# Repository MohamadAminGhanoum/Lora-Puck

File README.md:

# Lora-Puck
im planning on doing the lorapuck, while adding some simple and accurate sensors, which certainly will make this Lora Puck a lot more useful to me. Im planning to make 2 pcbs, one i keep at home that can track the temperature of e.g my room, and one i can take with me anywhere, and this will allow me to recieve signals from my home LORA, and i will be recieving it to my other LORA puc that i carry with me.
NOTE: as i am making it in the EU, i should follow the european law of max. 868 MHz, and not 915 MHz like USA

## Schematics:

## PCB:

## 3d pic of pcb:

## BOM

|Name             |Vendor                 |Quantity|Price in USD|Link                                                                                                                                                                                                    |
|-----------------|-----------------------|--------|------------|--------------------------------------------------------------------------------------------------------------------------------------------------------------------------------------------------------|
|PCB              |JLCPCB                 |5       |10          |JLCPCB                                                                                                                                                                                                  |
|100nF capacitor  |LCSC                   |12      |self-sourced|                                                                                                                                                                                                        |
|47nH inductor    |LCSC                   |1       |0.23        |https://www.lcsc.com/product-detail/C440659.html?spm=wm.gwc.xh.4.tp___wm.ddx.ssl.gwc&lcsc_vid=QAMKAlFUFVZXUFcCTgNWBgcHQQVYBlQEFlBWAlJSEgIxVlNeQ1RXU1ZUTlhZVzsOAxUeFF5JWBEPFBcWGBMaSQgFBAJABAsLWA%3D%3D  |
|HTU21D           |LCSC                   |2       |3.29        |https://www.lcsc.com/product-detail/C83479.html?spm=wm.gwc.xh.1.tp___wm.ddx.ssl.gwc&lcsc_vid=QAMKAlFUFVZXUFcCTgNWBgcHQQVYBlQEFlBWAlJSEgIxVlNeQ1RXU1ZUTlhZVzsOAxUeFF5JWBEPFBcWGBMaSQgFBAJABAsLWA%3D%3D   |
|RP2040           |LCSC                   |2       |1.99        |https://www.lcsc.com/product-detail/C2040.html?spm=wm.gwc.xh.2.tp___wm.ddx.ssl.gwc&lcsc_vid=QAMKAlFUFVZXUFcCTgNWBgcHQQVYBlQEFlBWAlJSEgIxVlNeQ1RXU1ZUTlhZVzsOAxUeFF5JWBEPFBcWGBMaSQgFBAJABAsLWA%3D%3D    |
|SX1262IMLTRT     |LCSC                   |2       |6.51        |https://www.lcsc.com/product-detail/C191341.html?spm=wm.gwc.xh.3.tp___wm.ddx.ssl.gwc&lcsc_vid=QAMKAlFUFVZXUFcCTgNWBgcHQQVYBlQEFlBWAlJSEgIxVlNeQ1RXU1ZUTlhZVzsOAxUeFF5JWBEPFBcWGBMaSQgFBAJABAsLWA%3D%3D  |
|                 |                       |        |            |                                                                                                                                                                                                        |
|AP2112K-3.3TRG1  |LCSC                   |5       |0.55        |https://www.lcsc.com/product-detail/C23380830.html?spm=wm.gwc.xh.5.tp___wm.ddx.ssl.gwc&lcsc_vid=QAMKAlFUFVZXUFcCTgNWBgcHQQVYBlQEFlBWAlJSEgIxVlNeQ1RXU1ZUTlhZVzsOAxUeFF5JWBEPFBcWGBMaSQgFBAJABAsLWA%3D%3D|
|W25Q128JVS       |LCSC                   |2       |5.6         |https://www.lcsc.com/product-detail/C97521.html?spm=wm.gwc.xh.6.tp___wm.ddx.ssl.gwc&lcsc_vid=QAMKAlFUFVZXUFcCTgNWBgcHQQVYBlQEFlBWAlJSEgIxVlNeQ1RXU1ZUTlhZVzsOAxUeFF5JWBEPFBcWGBMaSQgFBAJABAsLWA%3D%3D   |
|10uF capacitor   |LCSC                   |50      |1.75        |https://www.lcsc.com/product-detail/C1691.html?spm=wm.gwc.xh.7.tp___wm.ddx.ssl.gwc&lcsc_vid=QAMKAlFUFVZXUFcCTgNWBgcHQQVYBlQEFlBWAlJSEgIxVlNeQ1RXU1ZUTlhZVzsOAxUeFF5JWBEPFBcWGBMaSQgFBAJABAsLWA%3D%3D    |
|12nHz crystal    |LCSC                   |20      |0.43        |https://www.lcsc.com/product-detail/C1332832.html?spm=wm.gwc.xh.8.tp___wm.ddx.ssl.gwc&lcsc_vid=QAMKAlFUFVZXUFcCTgNWBgcHQQVYBlQEFlBWAlJSEgIxVlNeQ1RXU1ZUTlhZVzsOAxUeFF5JWBEPFBcWGBMaSQgFBAJABAsLWA%3D%3D |
|470nF cap        |LCSC                   |100     |1.15        |https://www.lcsc.com/product-detail/C105526.html?spm=wm.gwc.xh.9.tp___wm.ddx.ssl.gwc&lcsc_vid=QAMKAlFUFVZXUFcCTgNWBgcHQQVYBlQEFlBWAlJSEgIxVlNeQ1RXU1ZUTlhZVzsOAxUeFF5JWBEPFBcWGBMaSQgFBAJABAsLWA%3D%3D  |
|1k resistor      |LCSC                   |100     |0.76        |https://www.lcsc.com/product-detail/C2907002.html?spm=wm.gwc.xh.10.tp___wm.ddx.ssl.gwc&lcsc_vid=QAMKAlFUFVZXUFcCTgNWBgcHQQVYBlQEFlBWAlJSEgIxVlNeQ1RXU1ZUTlhZVzsOAxUeFF5JWBEPFBcWGBMaSQgFBAJABAsLWA%3D%3D|
|0900FM15K0039001E|LCSC                   |1       |0.61        |https://www.lcsc.com/product-detail/C7434807.html?spm=wm.gwc.xh.0.tp___wm.ddx.ssl.gwc&lcsc_vid=QAMKAlFUFVZXUFcCTgNWBgcHQQVYBlQEFlBWAlJSEgIxVlNeQ1RXU1ZUTlhZVzsOAxUeFF5JWBEPFBcWGBMaSQgFBAJABAsLWA%3D%3D |
|100 ohm resistor |LCSC                   |1       |selfsourced |                                                                                                                                                                                                        |
|32MHz            |LCSC                   |2       |selfsourced |                                                                                                                                                                                                        |
|3.3pF capacitor  |LCSC                   |100     |1.04        |https://www.lcsc.com/product-detail/C1660.html?spm=wm.gwc.xh.11.tp___wm.ddx.ssl.gwc&lcsc_vid=QAMKAlFUFVZXUFcCTgNWBgcHQQVYBlQEFlBWAlJSEgIxVlNeQ1RXU1ZUTlhZVzsOAxUeFF5JWBEPFBcWGBMaSQgFBAJABAsLWA%3D%3D   |
| 1uF capacitor   |LCSC                   |50      |1.09        |https://www.lcsc.com/product-detail/C29936.html?spm=wm.gwc.xh.12.tp___wm.ddx.ssl.gwc&lcsc_vid=QAMKAlFUFVZXUFcCTgNWBgcHQQVYBlQEFlBWAlJSEgIxVlNeQ1RXU1ZUTlhZVzsOAxUeFF5JWBEPFBcWGBMaSQgFBAJABAsLWA%3D%3D  |
|5.1k resistor    |LCSC                   |100     |0.24        |https://www.lcsc.com/product-detail/C2907044.html?spm=wm.gwc.xh.13.tp___wm.ddx.ssl.gwc&lcsc_vid=QAMKAlFUFVZXUFcCTgNWBgcHQQVYBlQEFlBWAlJSEgIxVlNeQ1RXU1ZUTlhZVzsOAxUeFF5JWBEPFBcWGBMaSQgFBAJABAsLWA%3D%3D|
|USB-c            |LCSC                   |20      |1.41        |https://www.lcsc.com/product-detail/C2765186.html?spm=wm.gwc.xh.14.tp___wm.ddx.ssl.gwc&lcsc_vid=QAMKAlFUFVZXUFcCTgNWBgcHQQVYBlQEFlBWAlJSEgIxVlNeQ1RXU1ZUTlhZVzsOAxUeFF5JWBEPFBcWGBMaSQgFBAJABAsLWA%3D%3D|
|switch           |LCSC                   |2       |selfsourced |                                                                                                                                                                                                        |
|BLM15AX102SN1D   |LCSC                   |100     |1.26        |https://www.lcsc.com/product-detail/C85815.html?spm=wm.gwc.xh.15.tp___wm.ddx.ssl.gwc&lcsc_vid=QAMKAlFUFVZXUFcCTgNWBgcHQQVYBlQEFlBWAlJSEgIxVlNeQ1RXU1ZUTlhZVzsOAxUeFF5JWBEPFBcWGBMaSQgFBAJABAsLWA%3D%3D  |
|27.4 ohm resistor|LCSC                   |2       |selfsourced |                                                                                                                                                                                                        |
|1nF capacitor    |LCSC                   |1       |1.46        |https://www.lcsc.com/product-detail/C100040.html?spm=wm.gwc.xh.20.tp___wm.ddx.ssl.gwc&lcsc_vid=QAMKAlFUFVZXUFcCTgNWBgcHQQVYBlQEFlBWAlJSEgIxVlNeQ1RXU1ZUTlhZVzsOAxUeFF5JWBEPFBcWGBMaSQgFBAJABAsLWA%3D%3D |
| 39pF cap        |LCSC                   |100     |0.52        |https://www.lcsc.com/product-detail/C107049.html?spm=wm.gwc.xh.16.tp___wm.ddx.ssl.gwc&lcsc_vid=QAMKAlFUFVZXUFcCTgNWBgcHQQVYBlQEFlBWAlJSEgIxVlNeQ1RXU1ZUTlhZVzsOAxUeFF5JWBEPFBcWGBMaSQgFBAJABAsLWA%3D%3D |
| 15pF cap        |LCSC                   |100     |0.57        |https://www.lcsc.com/product-detail/C107037.html?spm=wm.gwc.xh.17.tp___wm.ddx.ssl.gwc&lcsc_vid=QAMKAlFUFVZXUFcCTgNWBgcHQQVYBlQEFlBWAlJSEgIxVlNeQ1RXU1ZUTlhZVzsOAxUeFF5JWBEPFBcWGBMaSQgFBAJABAsLWA%3D%3D |
| 47pF cap        |LCSC                   |100     |0.61        |https://www.lcsc.com/product-detail/C105622.html?spm=wm.gwc.xh.18.tp___wm.ddx.ssl.gwc&lcsc_vid=QAMKAlFUFVZXUFcCTgNWBgcHQQVYBlQEFlBWAlJSEgIxVlNeQ1RXU1ZUTlhZVzsOAxUeFF5JWBEPFBcWGBMaSQgFBAJABAsLWA%3D%3D |
| 9.1nH inductor  |LCSC                   |50      |0.54        |https://www.lcsc.com/product-detail/C395094.html?spm=wm.gwc.xh.19.tp___wm.ddx.ssl.gwc&lcsc_vid=QAMKAlFUFVZXUFcCTgNWBgcHQQVYBlQEFlBWAlJSEgIxVlNeQ1RXU1ZUTlhZVzsOAxUeFF5JWBEPFBcWGBMaSQgFBAJABAsLWA%3D%3D |
| 10k resistor    |LCSC                   |100     |0.51        |https://www.lcsc.com/product-detail/C98220.html?spm=wm.gwc.dh.21.tp___wm.ddx.ssl.gwc&lcsc_vid=QAMKAlFUFVZXUFcCTgNWBgcHQQVYBlQEFlBWAlJSEgIxVlNeQ1RXU1ZUTlhZVzsOAxUeFF5JWBEPFBcWGBMaSQgFBAJABAsLWA%3D%3D  |
|PE4259           |LCSC                   |2       |1.41        |https://www.lcsc.com/product-detail/C470892.html?spm=wm.gwc.xh.22.tp___wm.ddx.ssl.gwc&lcsc_vid=QAMKAlFUFVZXUFcCTgNWBgcHQQVYBlQEFlBWAlJSEgIxVlNeQ1RXU1ZUTlhZVzsOAxUeFF5JWBEPFBcWGBMaSQgFBAJABAsLWA%3D%3D |
|15uH inductor    |LCSC                   |20      |0.73        |https://www.lcsc.com/product-detail/C486329.html?spm=wm.gwc.xh.23.tp___wm.ddx.ssl.gwc&lcsc_vid=QAMKAlFUFVZXUFcCTgNWBgcHQQVYBlQEFlBWAlJSEgIxVlNeQ1RXU1ZUTlhZVzsOAxUeFF5JWBEPFBcWGBMaSQgFBAJABAsLWA%3D%3D |
|                 |                       |        |            |                                                                                                                                                                                                        |
|                 |Total cost w. shipping:|50 usd  |            |                                                                                                                                                                                                        |

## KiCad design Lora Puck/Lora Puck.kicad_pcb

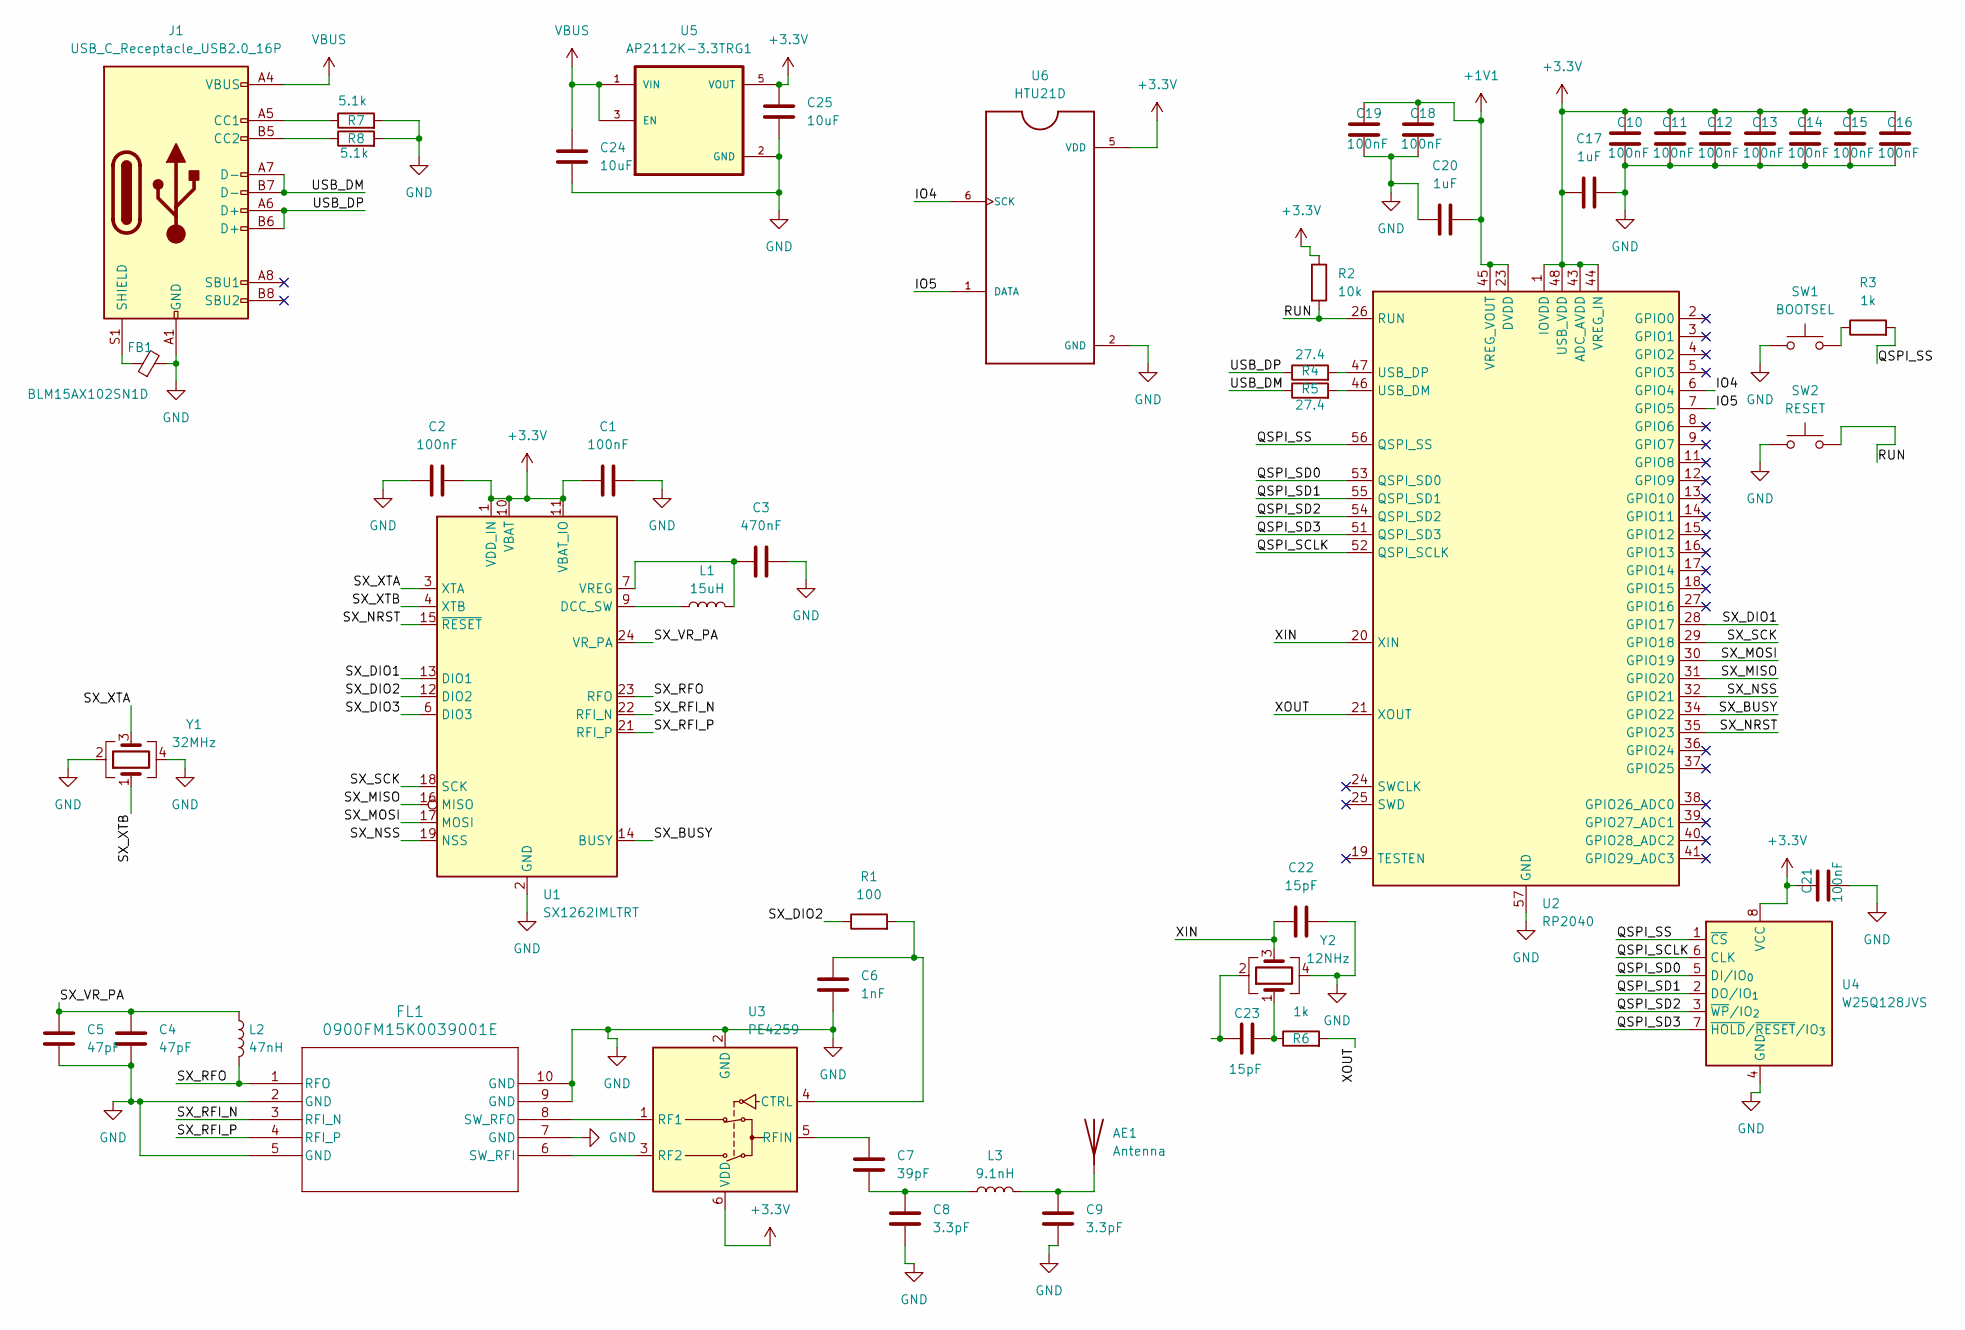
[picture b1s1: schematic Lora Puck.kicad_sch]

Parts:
AE1: Antenna; PinSocket_1x01_P2.54mm_Vertical
C1, C2, C10, C11, C12, C13, C14, C15, C16, C18, C19, C21: 100nF; C_0603_1608Metric
C3: 470nF; C_0603_1608Metric
C4, C5: 47pF; C_0603_1608Metric
C6: 1nF; C_0603_1608Metric
C7: 39pF; C_0603_1608Metric
C8, C9: 3.3pF; C_0603_1608Metric
C17, C20: 1uF; C_0603_1608Metric
C22, C23: 15pF; C_0603_1608Metric
C24, C25: 10uF; C_0603_1608Metric
FB1: BLM15AX102SN1D; L_0603_1608Metric
FL1: 0900FM15K0039001E; Balun_Johanson_0900FM15K0039
J1: USB_C_Receptacle_USB2.0_16P; USB_C_Receptacle_GCT_USB4105-xx-A_16P_TopMnt_Horizontal
L1: 15uH; L_0603_1608Metric
L2: 47nH; L_0603_1608Metric
L3: 9.1nH; L_0603_1608Metric
R1: 100; R_0603_1608Metric
R2: 10k; R_0603_1608Metric
R3, R6: 1k; R_0603_1608Metric
R4, R5: 27.4; R_0603_1608Metric
R7, R8: 5.1k; R_0603_1608Metric
SW1: BOOTSEL; SW_Tactile_SPST_NO_Straight_CK_PTS636Sx25SMTRLFS
SW2: RESET; SW_Tactile_SPST_NO_Straight_CK_PTS636Sx25SMTRLFS
U1: SX1262IMLTRT; QFN-24-1EP_4x4mm_P0.5mm_EP2.6x2.6mm
U2: RP2040; QFN-56-1EP_7x7mm_P0.4mm_EP3.2x3.2mm
U3: PE4259; SOT-363_SC-70-6
U4: W25Q128JVS; SOIC-8_5.3x5.3mm_P1.27mm
U5: AP2112K-3.3TRG1; SOT95P285X140-5N; PARTREV 2-2
U6: HTU21D; QFN100P300X300X100-7N
Y1: 32MHz; Crystal_SMD_3225-4Pin_3.2x2.5mm
Y2: 12NHz; Crystal_SMD_Abracon_ABM8G-4Pin_3.2x2.5mm

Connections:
+1V1: C18.1, C19.1, C20.2, U2.23 (DVDD), U2.45 (VREG_VOUT), U2.50 (DVDD)
+3.3V: C1.1, C2.2, C10.1, C11.1, C12.1, C13.1, C14.1, C15.1, C16.1, C17.1, C21.1, C25.1, R2.1, U1.1 (VDD_IN), U1.10 (VBAT), U1.11 (VBAT_IO), U2.1 (IOVDD), U2.10 (IOVDD), U2.22 (IOVDD), U2.33 (IOVDD), U2.42 (IOVDD), U2.43 (ADC_AVDD), U2.44 (VREG_IN), U2.48 (USB_VDD), U2.49 (IOVDD), U3.6 (VDD), U4.8 (VCC), U5.5 (VOUT), U6.5 (VDD)
/IO4: U2.6 (GPIO4), U6.6 (SCK)
/IO5: U2.7 (GPIO5), U6.1 (DATA)
/QSPI_SCLK: U2.52 (QSPI_SCLK), U4.6 (CLK)
/QSPI_SD0: U2.53 (QSPI_SD0), U4.5 (DI/IO_{0})
/QSPI_SD1: U2.55 (QSPI_SD1), U4.2 (DO/IO_{1})
/QSPI_SD2: U2.54 (QSPI_SD2), U4.3 (~WP/IO_{2})
/QSPI_SD3: U2.51 (QSPI_SD3), U4.7 (~HOLD/~RESET/IO_{3})
/QSPI_SS: R3.2, U2.56 (QSPI_SS), U4.1 (~CS)
/RUN: R2.2, SW2.2, U2.26 (RUN)
/SX_BUSY: U1.14 (BUSY), U2.34 (GPIO22)
/SX_DIO1: U1.13 (DIO1), U2.28 (GPIO17)
/SX_DIO2: R1.1, U1.12 (DIO2)
/SX_DIO3: U1.6 (DIO3)
/SX_MISO: U1.16 (MISO), U2.31 (GPIO20)
/SX_MOSI: U1.17 (MOSI), U2.30 (GPIO19)
/SX_NRST: U1.15 (~RESET), U2.35 (GPIO23)
/SX_NSS: U1.19 (NSS), U2.32 (GPIO21)
/SX_RFI_N: FL1.3 (RFI_N), U1.22 (RFI_N)
/SX_RFI_P: FL1.4 (RFI_P), U1.21 (RFI_P)
/SX_RFO: FL1.1 (RFO), L2.2, U1.23 (RFO)
/SX_SCK: U1.18 (SCK), U2.29 (GPIO18)
/SX_VR_PA: C4.1, C5.1, L2.1, U1.24 (VR_PA)
/SX_XTA: U1.3 (XTA), Y1.3
/SX_XTB: U1.4 (XTB), Y1.1
/USB_DM: J1.A7 (D-), J1.B7 (D-), R5.1
/USB_DP: J1.A6 (D+), J1.B6 (D+), R4.1
/XIN: C22.1, U2.20 (XIN), Y2.3
/XOUT: R6.2, U2.21 (XOUT)
GND: C1.2, C2.1, C3.2, C4.2, C5.2, C6.2, C8.1, C9.2, C10.2, C11.2, C12.2, C13.2, C14.2, C15.2, C16.2, C17.2, C18.2, C19.2, C20.1, C21.2, C22.2, C24.2, C25.2, FB1.2, FL1.2 (GND), FL1.5 (GND), FL1.7 (GND), FL1.9 (GND), FL1.10 (GND), J1.A1 (GND), J1.A12 (GND), J1.B1 (GND), J1.B12 (GND), R7.2, R8.2, SW1.1, SW2.1, U1.2 (GND), U1.5 (GND), U1.8 (GND), U1.20 (GND), U1.25 (GND), U2.57 (GND), U3.2 (GND), U4.4 (GND), U5.2 (GND), U6.2 (GND), U6.PAD (GND), Y1.2, Y1.4, Y2.4
unnamed: AE1.1 (A), C9.1, L3.2
unnamed: C7.1, C8.2, L3.1
unnamed: C23.1, Y2.2
unnamed: C23.2, R6.1, Y2.1
unnamed: FL1.6 (SW_RFI), U3.3 (RF2)
unnamed: FL1.8 (SW_RFO), U3.1 (RF1)
unnamed: J1.A5 (CC1), R7.1
unnamed: J1.B5 (CC2), R8.1
unnamed: FB1.1, J1.S1 (SHIELD)
unnamed: R3.1, SW1.2
unnamed: L1.1, U1.9 (DCC_SW)
unnamed: C3.1, L1.2, U1.7 (VREG)
unnamed: R5.2, U2.46 (USB_DM)
unnamed: R4.2, U2.47 (USB_DP)
unnamed: C6.1, R1.2, U3.4 (CTRL)
unnamed: C7.2, U3.5 (RFIN)
VBUS: C24.1, J1.A4 (VBUS), J1.A9 (VBUS), J1.B4 (VBUS), J1.B9 (VBUS), U5.1 (VIN), U5.3 (EN)

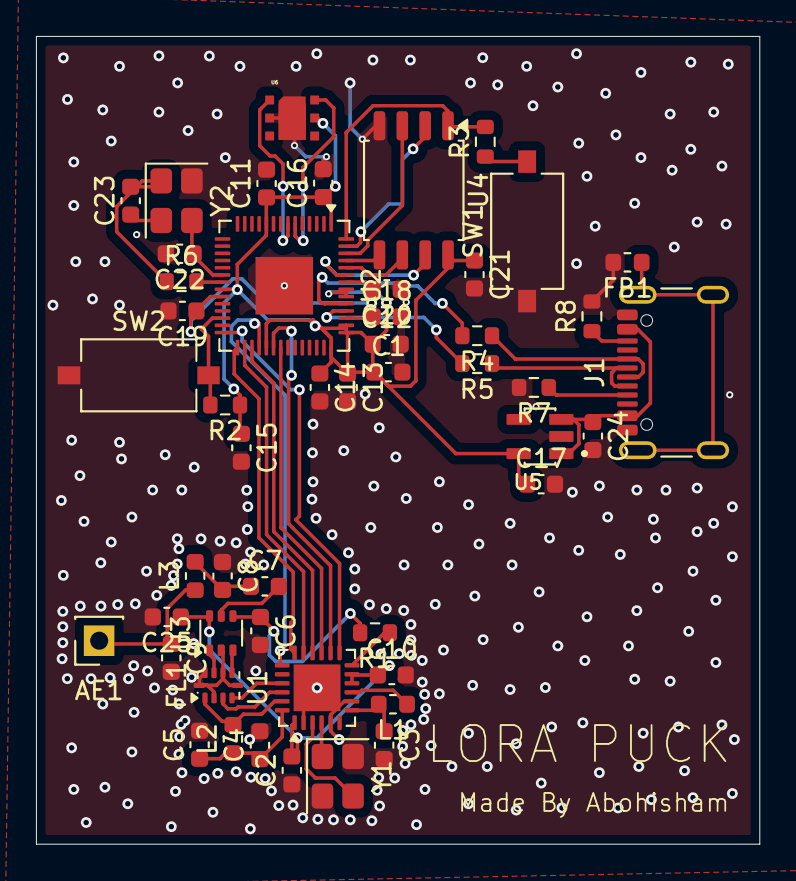
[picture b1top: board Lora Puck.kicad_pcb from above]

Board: 4 copper layers, 40.2 x 44.9 mm, 50 parts (0 on the bottom side), 47 nets.

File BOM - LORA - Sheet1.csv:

Name,Vendor,Quantity,Price in USD,Link
PCB,JLCPCB,5,10,JLCPCB
100nF capacitor,LCSC,12,self-sourced,
47nH inductor,LCSC,1,0.23,
HTU21D,LCSC,2,3.29,
RP2040,LCSC,2,1.99,
SX1262IMLTRT,LCSC,2,6.51,
0900FM15K0039001E,LCSC,2,1.21,
AP2112K-3.3TRG1,LCSC,5,0.55,
W25Q128JVS,LCSC,2,5.6,
10uF capacitor,LCSC,50,1.75,
12nHz crystal,LCSC,20,0.43,
470nF cap,LCSC,100,1.15,
1k resistor,LCSC,100,0.76,
0900FM15K0039001E,LCSC,1,0.61,
100 ohm resistor,LCSC,1,selfsourced,
32MHz,LCSC,2,selfsourced,
3.3pF capacitor,LCSC,100,1.04,
 1uF capacitor,LCSC,50,1.09,
5.1k resistor,LCSC,100,0.24,
USB-c,LCSC,20,1.41,
switch,LCSC,2,selfsourced,
BLM15AX102SN1D,LCSC,100,1.26,
27.4 ohm resistor,LCSC,2,selfsourced,
1nF capacitor,LCSC,1,1.46,
 39pF cap,LCSC,100,0.52,
 15pF cap,LCSC,100,0.57,
 47pF cap,LCSC,100,0.61,
 9.1nH inductor,LCSC,50,0.54,
 10k resistor,LCSC,100,0.51,
PE4259,LCSC,2,1.41,
15uH inductor,LCSC,20,0.73,
,,,,
,Total cost w. shipping:,50 usd,,
